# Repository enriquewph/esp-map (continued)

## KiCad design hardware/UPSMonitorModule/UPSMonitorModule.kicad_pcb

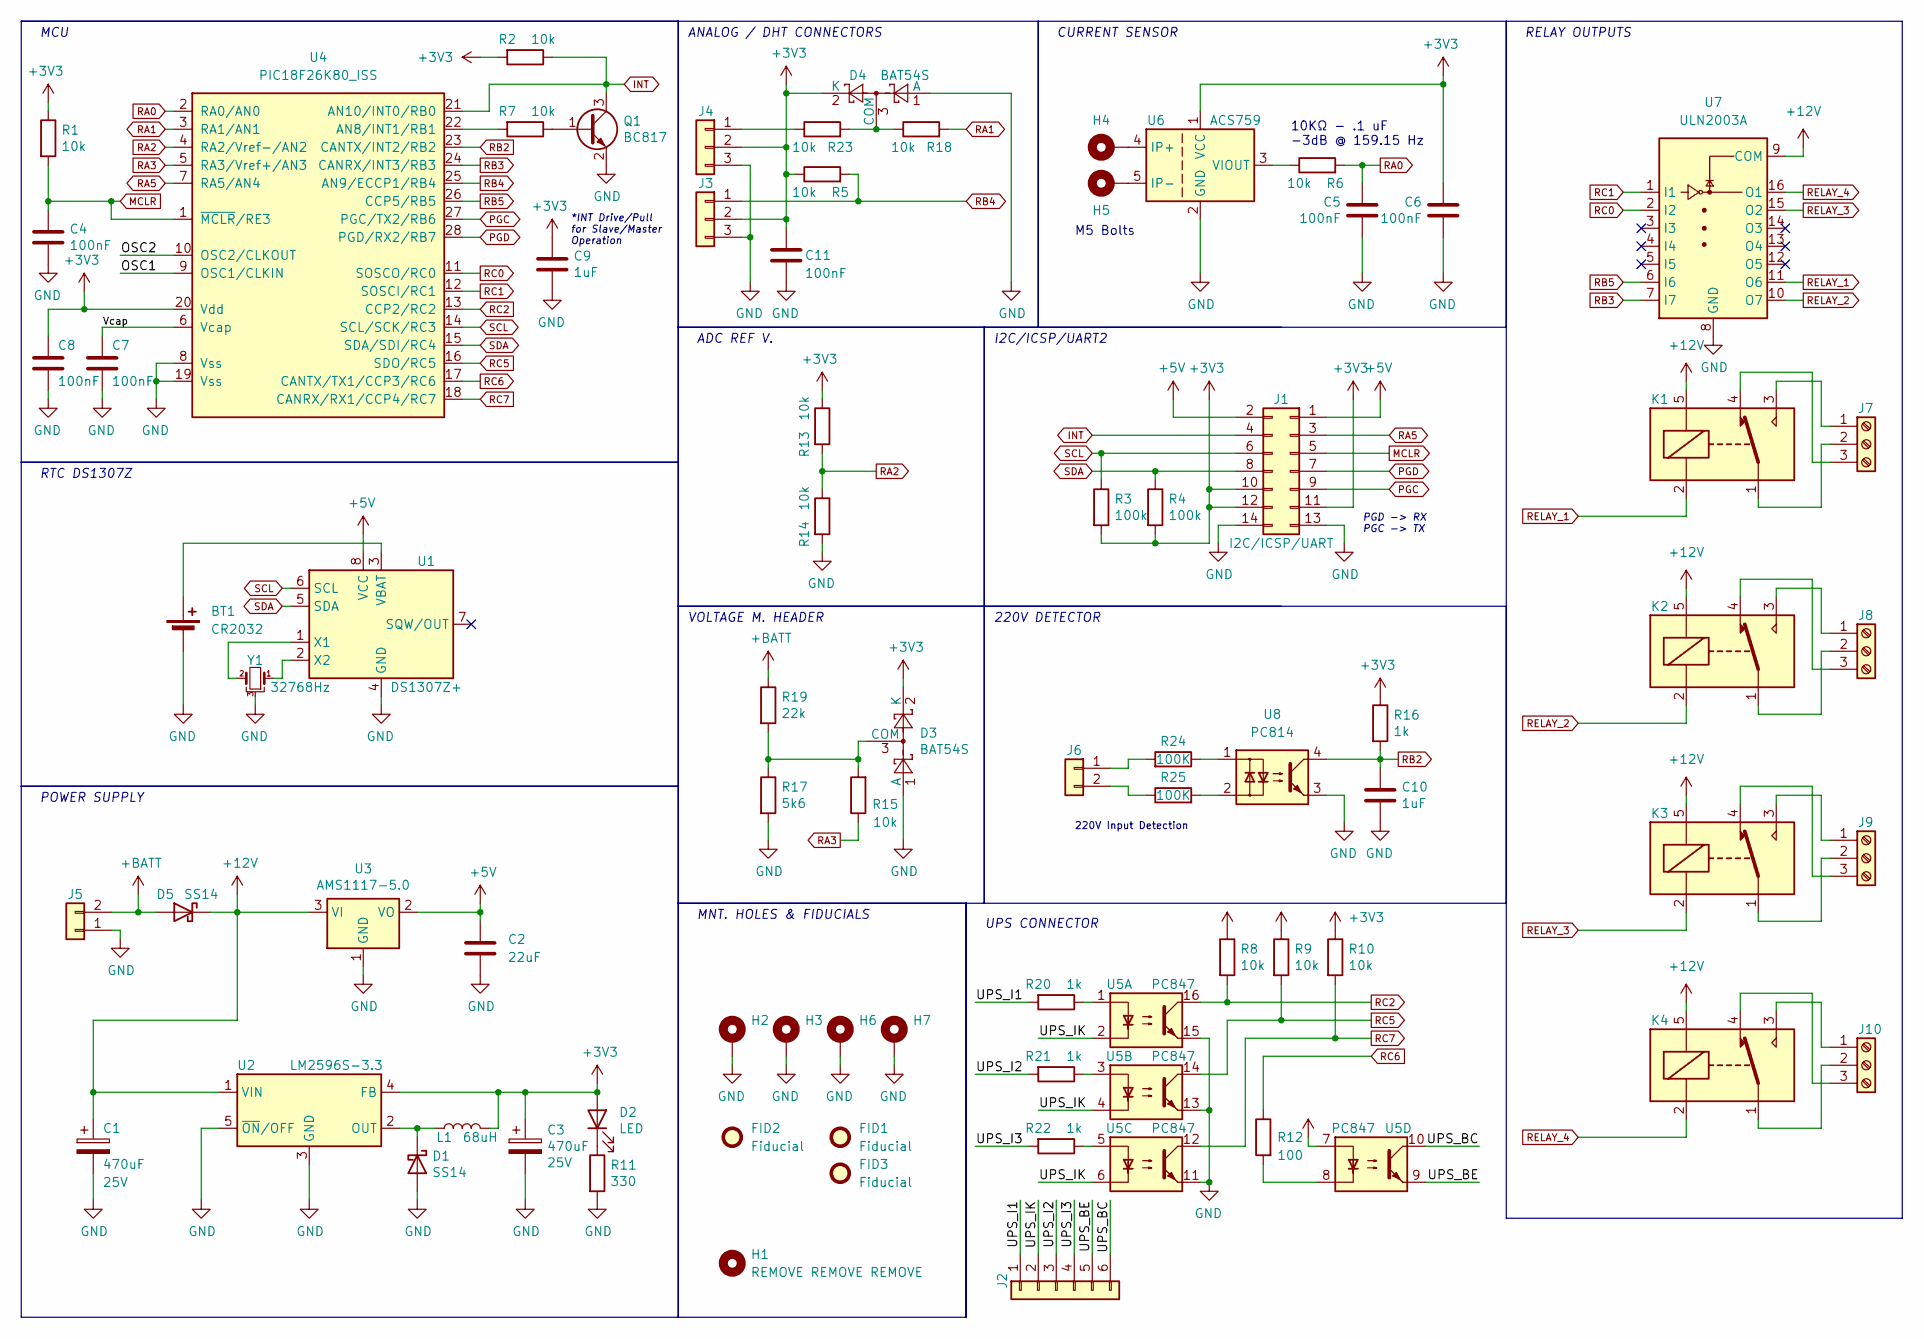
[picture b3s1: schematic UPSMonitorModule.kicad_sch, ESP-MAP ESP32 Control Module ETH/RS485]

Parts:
BT1: CR2032; BatteryHolder_CR2032
C1, C3: 470uF; CAP_10x10_SMD_THT; Voltage 25V
C2: 22uF; C_1812_4532Metric_Pad1.57x3.40mm_HandSolder
C4, C5, C6, C7, C8, C11: 100nF; C_1206_3216Metric_Pad1.33x1.80mm_HandSolder; Voltage 50V
C9, C10: 1uF; C_1206_3216Metric_Pad1.33x1.80mm_HandSolder; Voltage 50V
D1, D5: SS14; D_SMA_Handsoldering
D2: LED; LED_1206_3216Metric
D3, D4: BAT54S; SOT-23
FID1, FID2, FID3: Fiducial; Fiducial_0.5mm_Mask1mm
H1: REMOVE REMOVE REMOVE; ControlModule
H2, H3, H6, H7: MountingHole_Pad; MountingHole_3.5mm_Pad
H4, H5: MountingHole_Pad; MountingHole_5.3mm_M5_Pad_Via
J1: I2C/ICSP/UART; PinHeader_2x07_P2.54mm_Vertical_19mmh
J2: Conn_01x06; Molex_KK-254_AE-6410-06A_1x06_P2.54mm_Vertical
J3, J4: Conn_01x03; Molex_KK-254_AE-6410-03A_1x03_P2.54mm_Vertical
J5, J6: Conn_01x02; TerminalBlock-Bornier-2_P5.08mm
J7, J8, J9, J10: Screw_Terminal_01x03; TerminalBlock-Bornier-3_P5.08mm
K1, K2, K3, K4: RELAY; Relay_SPDT_SANYOU_SRD_Series_Form_C
L1: 68uH; L_12x12mm_H8mm
Q1: BC817; SOT-23
R1, R2, R5, R6, R7, R8, R9, R10, R13, R14, R15, R18, R23: 10k; R_1206_3216Metric
R3, R4: 100k; R_1206_3216Metric
R11: 330; R_1206_3216Metric
R12: 100; R_1206_3216Metric
R16, R20, R21, R22: 1k; R_1206_3216Metric
R17: 5k6; R_Axial_DIN0207_L6.3mm_D2.5mm_P2.54mm_Vertical
R19: 22k; R_Axial_DIN0207_L6.3mm_D2.5mm_P2.54mm_Vertical
R24, R25: 100K; R_Axial_DIN0309_L9.0mm_D3.2mm_P5.08mm_Vertical
U1: DS1307Z+; SOIC-8_3.9x4.9mm_P1.27mm
U2: LM2596S-3.3; TO-263-5_TabPin3
U3: AMS1117-5.0; SOT-223-3_TabPin2
U4: PIC18F26K80_ISS; SSOP-28_5.3x10.2mm_P0.65mm
U5: PC847; SMDIP-16_W9.53mm
U6: ACS759; Allegro_CB_PFF
U7: ULN2003A; SOIC-16_3.9x9.9mm_P1.27mm
U8: PC814; SMDIP-4_W9.53mm
Y1: 32768Hz; Crystal_C38-LF_D3.0mm_L8.0mm_Horizontal_1EP_style1

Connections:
+3V3: C3.1, C6.1, C8.1, C9.1, C11.1, D2.2 (A), D3.2 (K), D4.2 (K), J1.10, J1.11, J1.12, J3.2, J4.2, L1.2, R1.1, R2.2, R3.2, R4.2, R5.1, R8.1, R9.1, R10.1, R13.1, R16.1, U2.4 (FB), U4.20 (Vdd), U5.7, U6.1 (VCC)
+5V: C2.1, J1.1, J1.2, U1.8 (VCC), U3.2 (VO)
+12V: C1.1, D5.1 (K), K1.5, K2.5, K3.5, K4.5, U2.1 (VIN), U3.3 (VI), U7.9 (COM)
+BATT: D5.2 (A), J5.2, R19.1
/OSC1: U4.9 (OSC1/CLKIN)
/OSC2: U4.10 (OSC2/CLKOUT)
/UPS_BC: J2.6, U5.10
/UPS_BE: J2.5, U5.9
/UPS_I1: J2.1, R20.2
/UPS_I2: J2.3, R21.2
/UPS_I3: J2.4, R22.2
/UPS_IK: J2.2, U5.2, U5.4, U5.6
/Vcap: C7.1, U4.6 (Vcap)
GND: BT1.2 (-), C1.2, C2.2, C3.2, C4.2, C5.2, C6.2, C7.2, C8.2, C9.2, C10.2, C11.2, D1.2 (A), D3.1 (A), D4.1 (A), H2.1, H3.1, H6.1, H7.1, J1.13, J1.14, J3.3, J4.3, J5.1, Q1.2 (E), R11.2, R14.2, R17.2, U1.4 (GND), U2.3 (GND), U2.5 (~ON/OFF), U3.1 (GND), U4.8 (Vss), U4.19 (Vss), U5.11, U5.13, U5.15, U6.2 (GND), U7.8 (GND), U8.3, Y1.3
INT: J1.4, Q1.3 (C), R2.1, U4.21 (AN10/INT0/RB0)
MCLR: C4.1, J1.5, R1.2, U4.1 (~MCLR/RE3)
unnamed: BT1.1 (+), U1.3 (VBAT)
unnamed: D1.1 (K), L1.1, U2.2 (OUT)
unnamed: D2.1 (K), R11.1
unnamed: D4.3 (COM), R18.1, R23.2
unnamed: D3.3 (COM), R15.2, R17.1, R19.2
unnamed: J4.1, R23.1
unnamed: J6.1, R24.2
unnamed: J6.2, R25.1
unnamed: J7.1, K1.3
unnamed: J7.2, K1.1
unnamed: J7.3, K1.4
unnamed: J8.1, K2.3
unnamed: J8.2, K2.1
unnamed: J8.3, K2.4
unnamed: J9.1, K3.3
unnamed: J9.2, K3.1
unnamed: J9.3, K3.4
unnamed: J10.1, K4.3
unnamed: J10.2, K4.1
unnamed: J10.3, K4.4
unnamed: Q1.1 (B), R7.1
unnamed: R20.1, U5.1
unnamed: R21.1, U5.3
unnamed: R22.1, U5.5
unnamed: R24.1, U8.1
unnamed: R25.2, U8.2
unnamed: R12.2, U5.8
unnamed: R7.2, U4.22 (AN8/INT1/RB1)
unnamed: U1.1 (X1), Y1.2
unnamed: U1.2 (X2), Y1.1
unnamed: H4.1, U6.4 (IP+)
unnamed: H5.1, U6.5 (IP-)
unnamed: R6.1, U6.3 (VIOUT)
PGC: J1.9, U4.27 (PGC/TX2/RB6)
PGD: J1.7, U4.28 (PGD/RX2/RB7)
RA0: C5.1, R6.2, U4.2 (RA0/AN0)
RA1: R18.2, U4.3 (RA1/AN1)
RA2: R13.2, R14.1, U4.4 (RA2/Vref-/AN2)
RA3: R15.1, U4.5 (RA3/Vref+/AN3)
RA5: J1.3, U4.7 (RA5/AN4)
RB2: C10.1, R16.2, U4.23 (CANTX/INT2/RB2), U8.4
RB3: U4.24 (CANRX/INT3/RB3), U7.7 (I7)
RB4: J3.1, R5.2, U4.25 (AN9/ECCP1/RB4)
RB5: U4.26 (CCP5/RB5), U7.6 (I6)
RC0: U4.11 (SOSCO/RC0), U7.2 (I2)
RC1: U4.12 (SOSCI/RC1), U7.1 (I1)
RC2: R8.2, U4.13 (CCP2/RC2), U5.16
RC5: R9.2, U4.16 (SDO/RC5), U5.14
RC6: R12.1, U4.17 (CANTX/TX1/CCP3/RC6)
RC7: R10.2, U4.18 (CANRX/RX1/CCP4/RC7), U5.12
RELAY_1: K1.2, U7.11 (O6)
RELAY_2: K2.2, U7.10 (O7)
RELAY_3: K3.2, U7.15 (O2)
RELAY_4: K4.2, U7.16 (O1)
SCL: J1.6, R3.1, U1.6 (SCL), U4.14 (SCL/SCK/RC3)
SDA: J1.8, R4.1, U1.5 (SDA), U4.15 (SDA/SDI/RC4)

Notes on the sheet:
I2C/ICSP/UART2
VOLTAGE M. HEADER
UPS CONNECTOR
ANALOG / DHT CONNECTORS
220V DETECTOR
CURRENT SENSOR
PGD -> RX PGC -> TX
10KΩ - .1 uF -3dB @ 159.15 Hz
MNT. HOLES & FIDUCIALS
RTC DS1307Z
POWER SUPPLY
M5 Bolts
RELAY OUTPUTS
ADC REF V.
*INT Drive/Pull for Slave/Master Operation
220V Input Detection
MCU

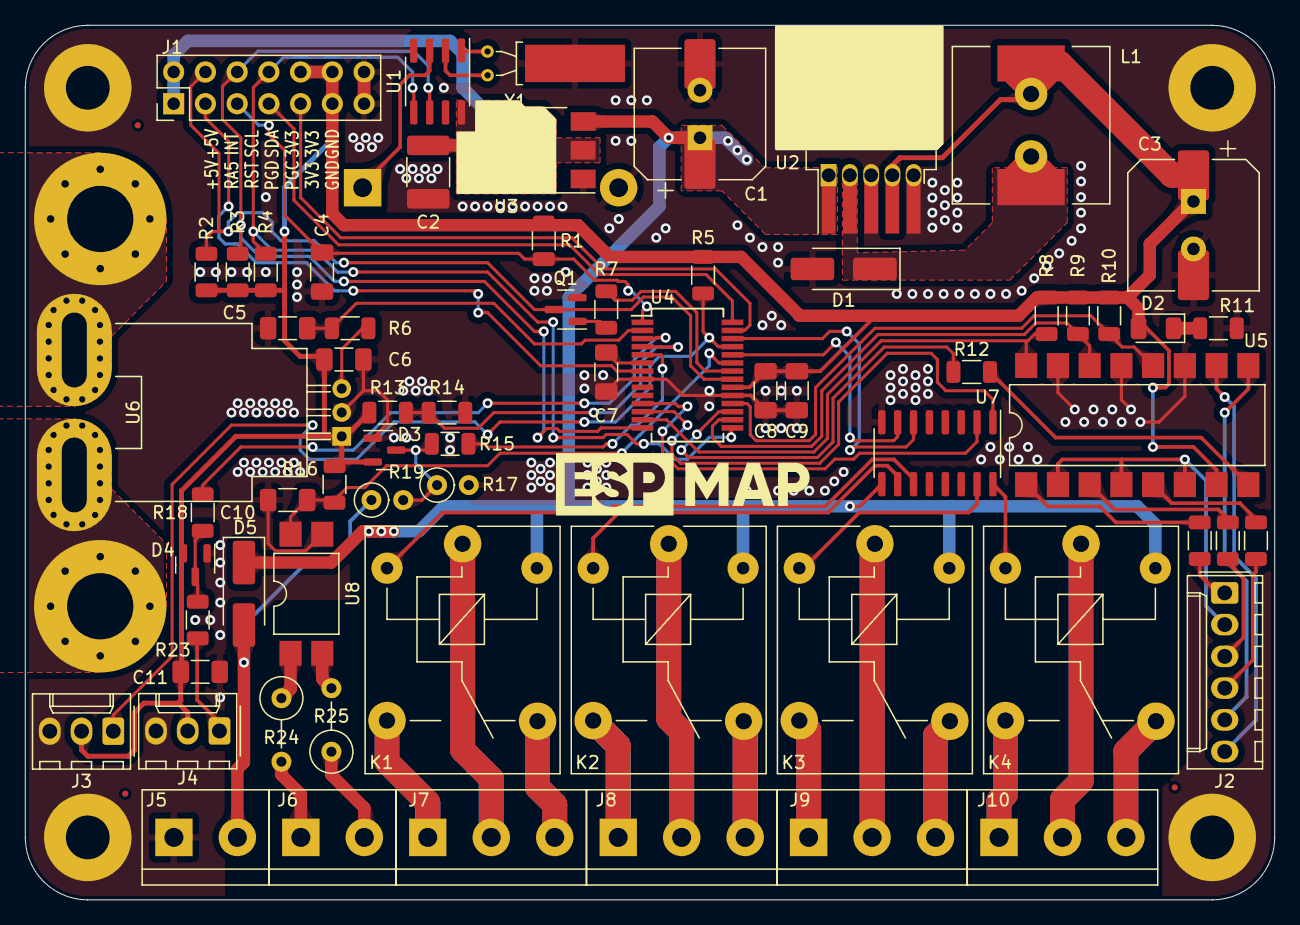
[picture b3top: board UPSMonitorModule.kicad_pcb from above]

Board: 2 copper layers, 100.0 x 70.0 mm, 76 parts (1 on the bottom side), 70 nets.

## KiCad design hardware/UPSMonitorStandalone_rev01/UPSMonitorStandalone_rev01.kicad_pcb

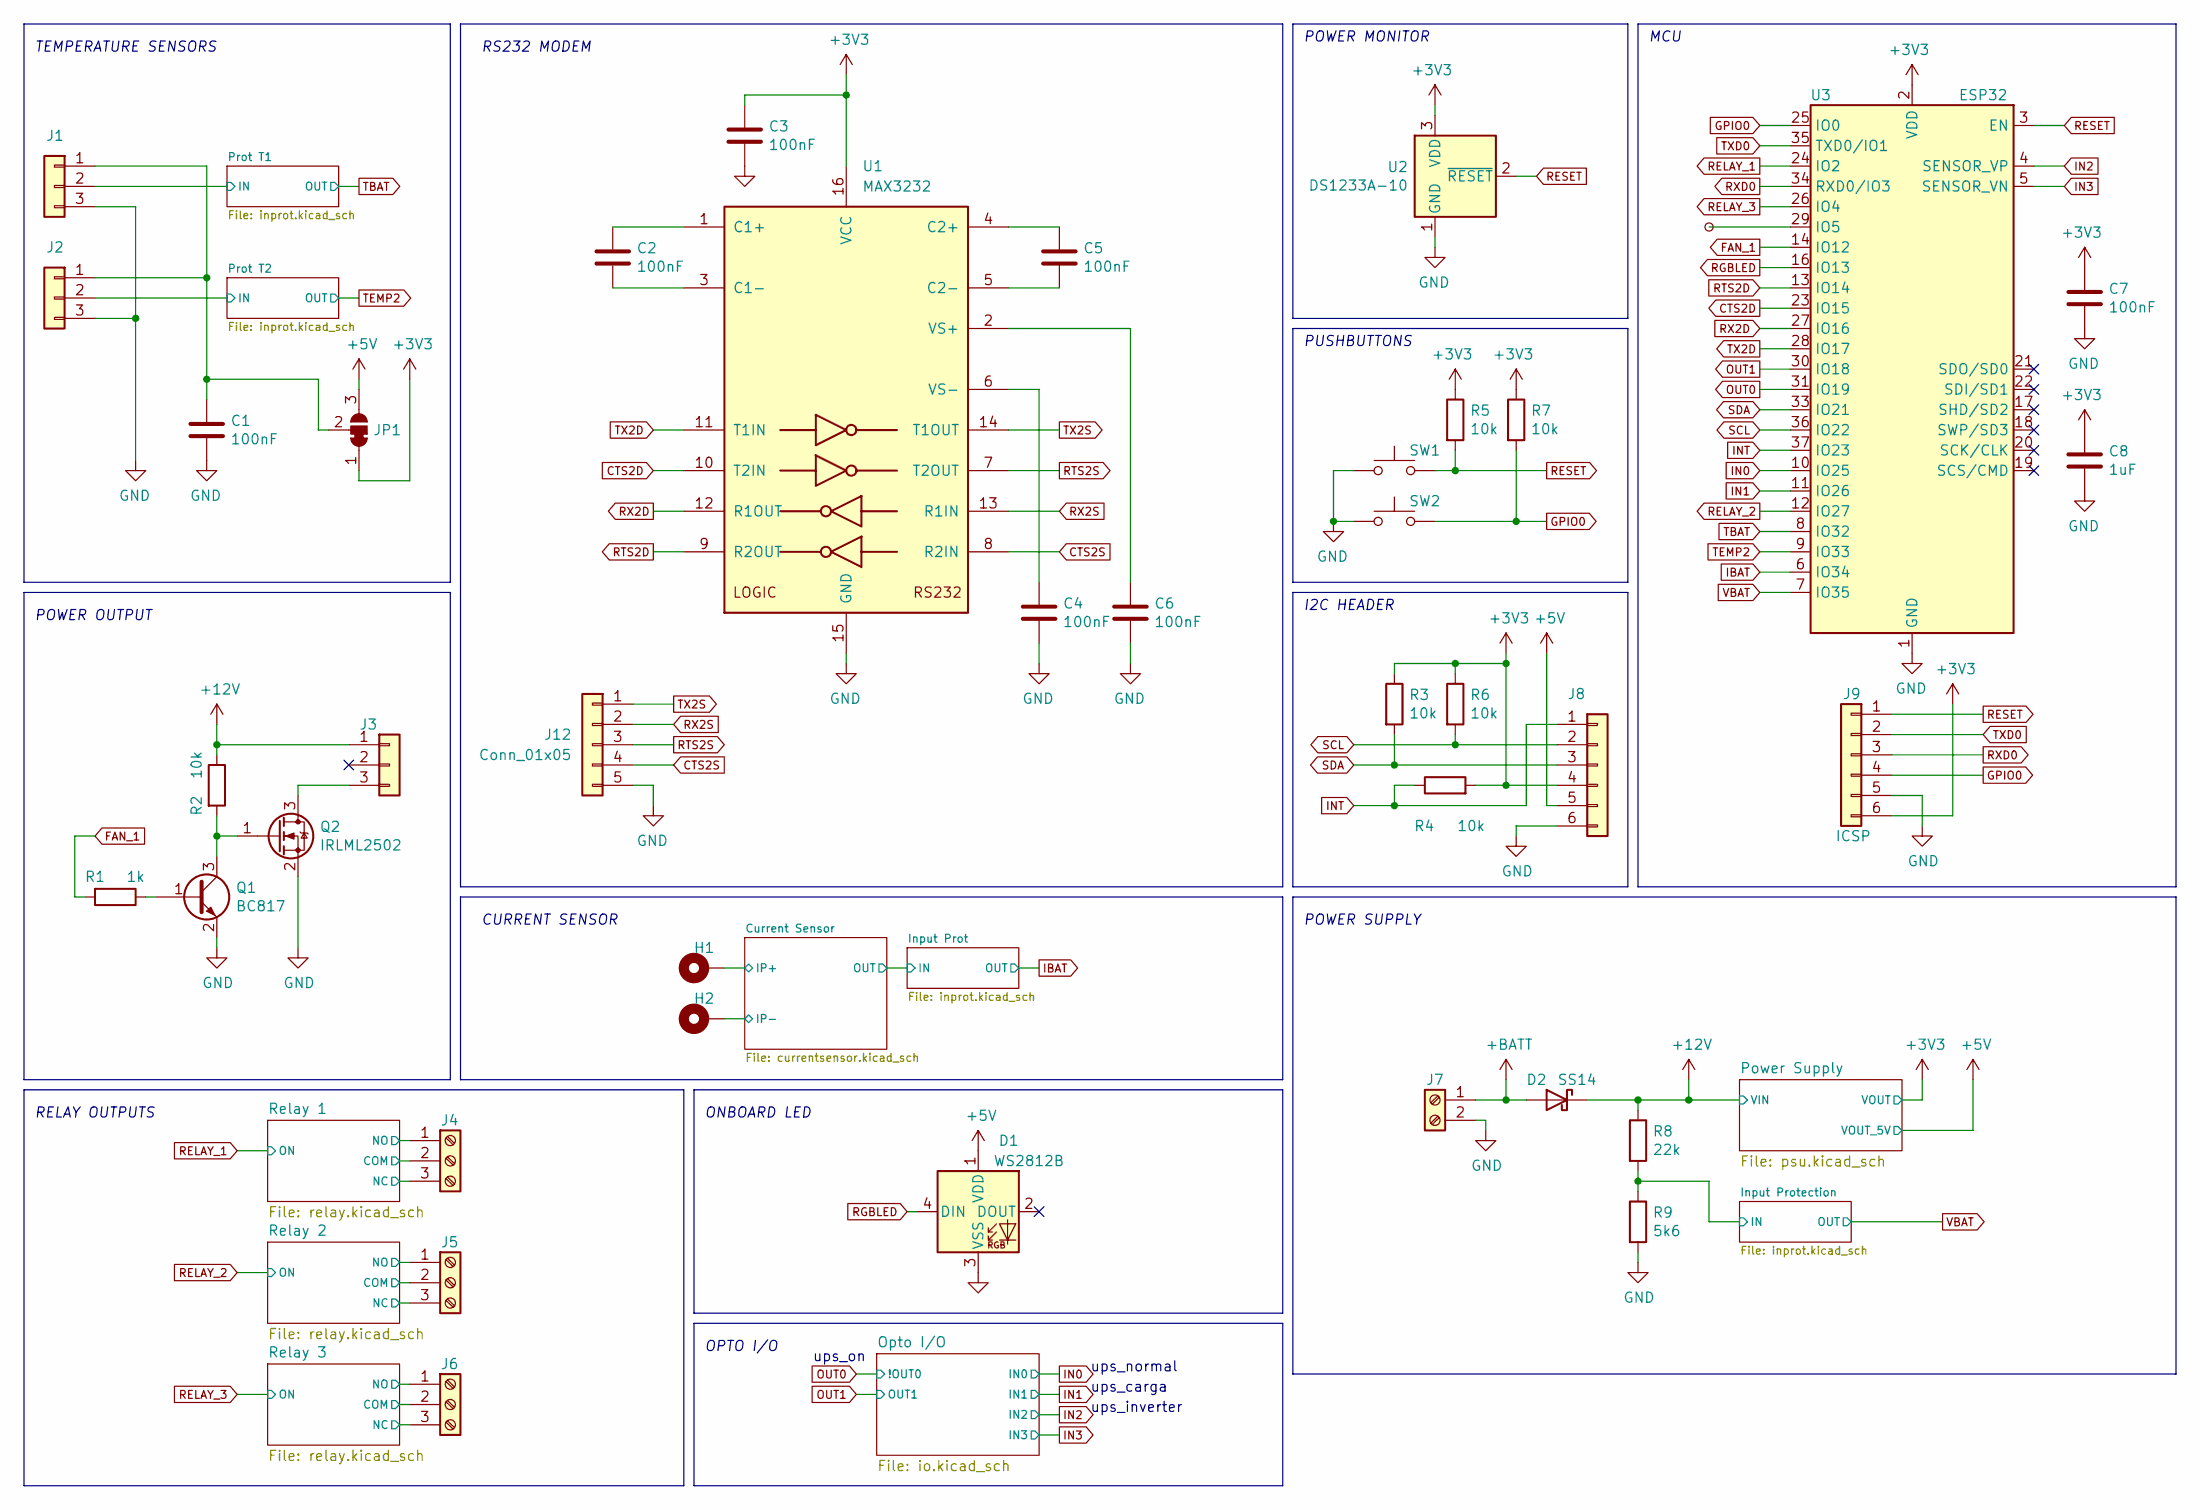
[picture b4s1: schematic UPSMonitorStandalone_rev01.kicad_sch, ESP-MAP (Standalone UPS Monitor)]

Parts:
C1, C7: 100nF; C_1206_3216Metric_Pad1.33x1.80mm_HandSolder; Voltage 50V
C2, C3, C4, C5, C6: 100nF; C_0603_1608Metric_Pad1.08x0.95mm_HandSolder; Voltage 50V
C8: 1uF; C_1206_3216Metric_Pad1.33x1.80mm_HandSolder; Voltage 50V
D1: WS2812B; LED_WS2812B_PLCC4_5.0x5.0mm_P3.2mm
D2: SS14; D_SMA_Handsoldering
H1, H2: MountingHole_Pad; MountingHole_4mm_Pad_Via
J1, J2, J3: Conn_01x03; Molex_KK-254_AE-6410-03A_1x03_P2.54mm_Vertical
J4, J5, J6: Screw_Terminal_01x03; TerminalBlock_bornier-3_P5.08mm
J7: Screw_Terminal_01x02; TerminalBlock_bornier-2_P5.08mm
J8: Conn_01x06; Molex_KK-254_AE-6410-06A_1x06_P2.54mm_Vertical
J9: ICSP; PinSocket_1x06_P2.54mm_Vertical
J12: Conn_01x05; PinSocket_1x05_P2.54mm_Vertical
JP1: SolderJumper_3_Bridged12; SolderJumper-3_P1.3mm_Open_RoundedPad1.0x1.5mm_NumberLabels
Q1: BC817; SOT-23
Q2: IRLML2502; SOT-23
R1: 1k; R_1206_3216Metric
R2, R3, R4, R5, R6, R7: 10k; R_1206_3216Metric
R8: 22k; R_1206_3216Metric
R9: 5k6; R_1206_3216Metric
SW1, SW2: SW_Push; SW_PUSH_6mm
TP1: TestPoint_Small; TestPoint_Pad_D1.0mm
U1: MAX3232; SOIC-16_3.9x9.9mm_P1.27mm
U2: DS1233A-10; TO-92
U3: ESP32; ESP32-WROOM-32

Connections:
+3V3: C3.1, C7.1, C8.1, J8.4, J9.6, JP1.1 (A), R3.1, R4.2, R5.1, R6.1, R7.1, U1.16 (VCC), U2.3 (VDD), U3.2 (VDD); also elsewhere on the board
+5V: D1.1 (VDD), J8.5, JP1.3 (B); also elsewhere on the board
+12V: D2.1 (K), J3.1, R2.1, R8.1; also elsewhere on the board
+BATT: D2.2 (A), J7.1
/Current Sensor/IP+: H1.1; also elsewhere on the board
/Current Sensor/IP-: H2.1; also elsewhere on the board
/Input Protection/IN: R8.2, R9.1; also elsewhere on the board
/Prot T1/IN: J1.2; also elsewhere on the board
/Prot T2/IN: J2.2; also elsewhere on the board
/Relay 1/COM: J4.2; also elsewhere on the board
/Relay 1/NC: J4.3; also elsewhere on the board
/Relay 1/NO: J4.1; also elsewhere on the board
/Relay 2/COM: J5.2; also elsewhere on the board
/Relay 2/NC: J5.3; also elsewhere on the board
/Relay 2/NO: J5.1; also elsewhere on the board
/Relay 3/COM: J6.2; also elsewhere on the board
/Relay 3/NC: J6.3; also elsewhere on the board
/Relay 3/NO: J6.1; also elsewhere on the board
CTS2D: U1.10 (T2IN), U3.23 (IO15)
CTS2S: J12.4, U1.8 (R2IN)
FAN_1: R1.2, U3.14 (IO12)
GND: C1.2, C3.2, C4.2, C6.2, C7.2, C8.2, D1.3 (VSS), J1.3, J2.3, J7.2, J8.6, J9.5, J12.5, Q1.2 (E), Q2.2 (S), R9.2, SW1.1, SW2.1, U1.15 (GND), U2.1 (GND), U3.1 (GND), U3.15 (GND), U3.38 (GND), U3.39 (GND); also elsewhere on the board
GPIO0: J9.4, R7.2, SW2.2, U3.25 (IO0)
IBAT: U3.6 (IO34); also elsewhere on the board
IN0: U3.10 (IO25); also elsewhere on the board
IN1: U3.11 (IO26); also elsewhere on the board
IN2: U3.4 (SENSOR_VP); also elsewhere on the board
IN3: U3.5 (SENSOR_VN); also elsewhere on the board
INT: J8.1, R4.1, U3.37 (IO23)
unnamed: C1.1, J1.1, J2.1, JP1.2 (C)
unnamed: J3.3, Q2.3 (D)
unnamed: Q1.1 (B), R1.1
unnamed: Q1.3 (C), Q2.1 (G), R2.2
unnamed: C2.1, U1.1 (C1+)
unnamed: C2.2, U1.3 (C1-)
unnamed: C5.1, U1.4 (C2+)
unnamed: C5.2, U1.5 (C2-)
unnamed: C6.1, U1.2 (VS+)
unnamed: C4.1, U1.6 (VS-)
unnamed: TP1.1, U3.29 (IO5)
OUT0: U3.31 (IO19); also elsewhere on the board
OUT1: U3.30 (IO18); also elsewhere on the board
RELAY_1: U3.24 (IO2); also elsewhere on the board
RELAY_2: U3.12 (IO27); also elsewhere on the board
RELAY_3: U3.26 (IO4); also elsewhere on the board
RESET: J9.1, R5.2, SW1.2, U2.2 (~RESET), U3.3 (EN)
RGBLED: D1.4 (DIN), U3.16 (IO13)
RTS2D: U1.9 (R2OUT), U3.13 (IO14)
RTS2S: J12.3, U1.7 (T2OUT)
RX2D: U1.12 (R1OUT), U3.27 (IO16)
RX2S: J12.2, U1.13 (R1IN)
RXD0: J9.3, U3.34 (RXD0/IO3)
SCL: J8.2, R6.2, U3.36 (IO22)
SDA: J8.3, R3.2, U3.33 (IO21)
TBAT: U3.8 (IO32); also elsewhere on the board
TEMP2: U3.9 (IO33); also elsewhere on the board
TX2D: U1.11 (T1IN), U3.28 (IO17)
TX2S: J12.1, U1.14 (T1OUT)
TXD0: J9.2, U3.35 (TXD0/IO1)
VBAT: U3.7 (IO35); also elsewhere on the board

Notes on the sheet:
POWER SUPPLY
I2C HEADER
ONBOARD LED
ups_normal
PUSHBUTTONS
POWER OUTPUT
ups_carga
ups_on
POWER MONITOR
RELAY OUTPUTS
MCU
RS232 MODEM
OPTO I/O
ups_inverter
CURRENT SENSOR
TEMPERATURE SENSORS

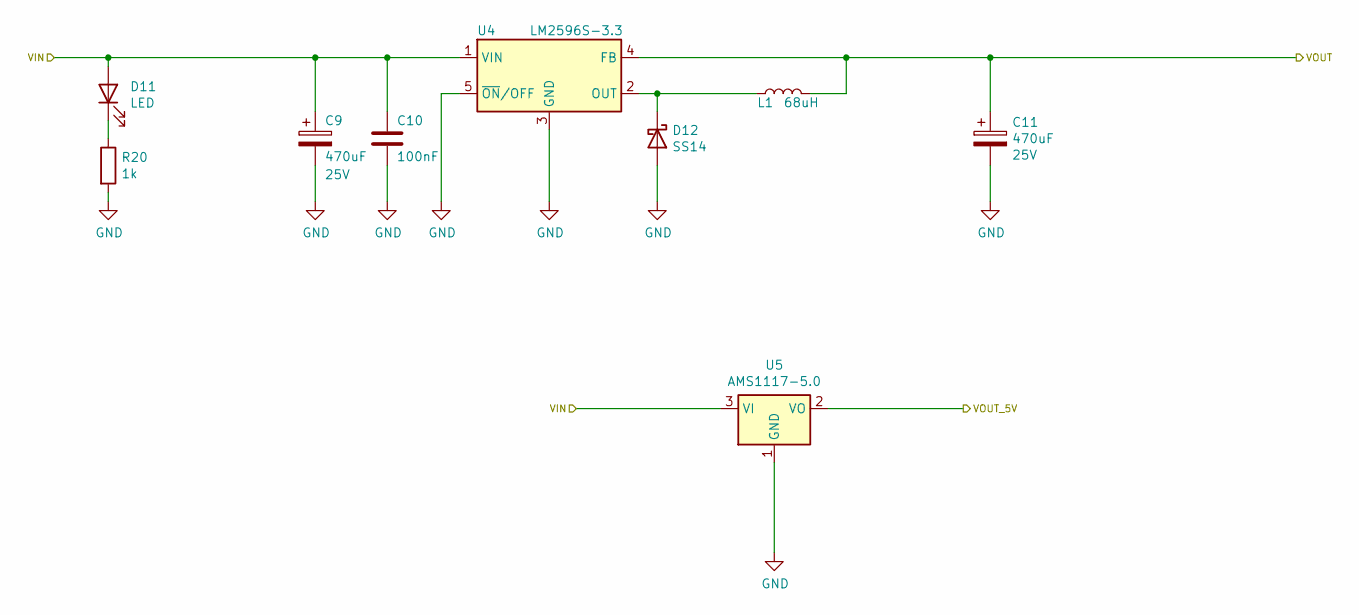
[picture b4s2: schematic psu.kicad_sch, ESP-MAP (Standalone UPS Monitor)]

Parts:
C9, C11: 470uF; CAP_10x10_SMD_THT; Voltage 25V
C10: 100nF; C_1206_3216Metric_Pad1.33x1.80mm_HandSolder; Voltage 50V
D11: LED; LED_1206_3216Metric
D12: SS14; D_SMA_Handsoldering
L1: 68uH; L_12x12mm_H8mm
R20: 1k; R_1206_3216Metric
U4: LM2596S-3.3; TO-263-5_TabPin3
U5: AMS1117-5.0; SOT-223-3_TabPin2

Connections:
+3V3: C11.1, L1.2, U4.4 (FB); also elsewhere on the board
+5V: U5.2 (VO); also elsewhere on the board
+12V: C9.1, C10.1, D11.2 (A), U4.1 (VIN), U5.3 (VI); also elsewhere on the board
GND: C9.2, C10.2, C11.2, D12.2 (A), R20.2, U4.3 (GND), U4.5 (~ON/OFF), U5.1 (GND); also elsewhere on the board
unnamed: D11.1 (K), R20.1
unnamed: D12.1 (K), L1.1, U4.2 (OUT)

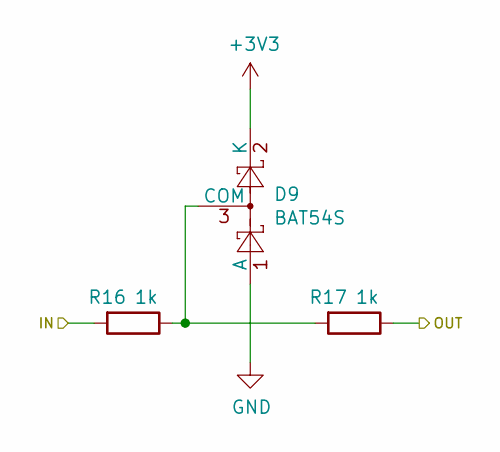
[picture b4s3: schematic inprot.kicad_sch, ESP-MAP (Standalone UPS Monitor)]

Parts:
D9: BAT54S; SOT-23
R16, R17: 1k; R_1206_3216Metric

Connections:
+3V3: D9.2 (K); also elsewhere on the board
/Prot T1/IN: R16.2; also elsewhere on the board
GND: D9.1 (A); also elsewhere on the board
unnamed: D9.3 (COM), R16.1, R17.2
TBAT: R17.1; also elsewhere on the board

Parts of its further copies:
D10, D13, D14: BAT54S; SOT-23
R18, R19, R21, R22, R25, R26: 1k; R_1206_3216Metric

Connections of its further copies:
+3V3: D10.2 (K), D13.2 (K), D14.2 (K); also elsewhere on the board
/Current Sensor/OUT: R25.2; also elsewhere on the board
/Input Protection/IN: R21.2; also elsewhere on the board
/Prot T2/IN: R18.2; also elsewhere on the board
GND: D10.1 (A), D13.1 (A), D14.1 (A); also elsewhere on the board
IBAT: R26.1; also elsewhere on the board
unnamed: D10.3 (COM), R18.1, R19.2
unnamed: D13.3 (COM), R21.1, R22.2
unnamed: D14.3 (COM), R25.1, R26.2
TEMP2: R19.1; also elsewhere on the board
VBAT: R22.1; also elsewhere on the board

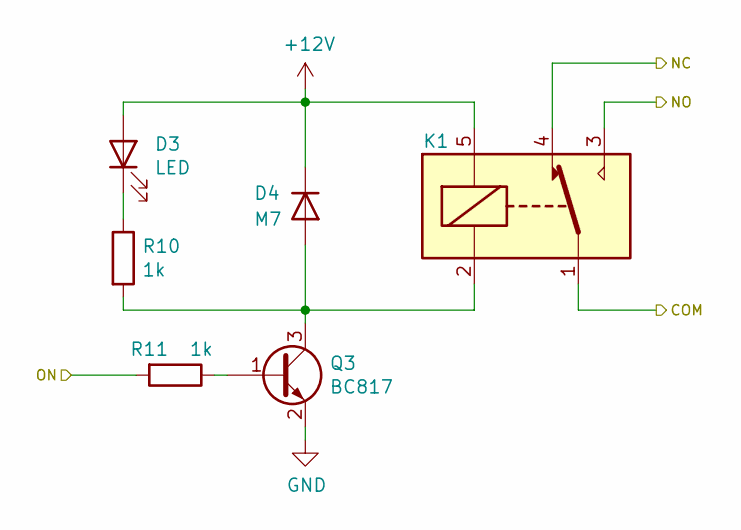
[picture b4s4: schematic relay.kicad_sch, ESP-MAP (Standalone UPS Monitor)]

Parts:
D3: LED; LED_1206_3216Metric
D4: M7; D_SMA_Handsoldering
K1: RELAY; Relay_SPDT_SANYOU_SRD_Series_Form_C
Q3: BC817; SOT-23
R10, R11: 1k; R_1206_3216Metric

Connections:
+12V: D3.2 (A), D4.1 (K), K1.5; also elsewhere on the board
/Relay 1/COM: K1.1; also elsewhere on the board
/Relay 1/NC: K1.4; also elsewhere on the board
/Relay 1/NO: K1.3; also elsewhere on the board
GND: Q3.2 (E); also elsewhere on the board
unnamed: D3.1 (K), R10.1
unnamed: D4.2 (A), K1.2, Q3.3 (C), R10.2
unnamed: Q3.1 (B), R11.1
RELAY_1: R11.2; also elsewhere on the board

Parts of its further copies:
D5, D7: LED; LED_1206_3216Metric
D6, D8: M7; D_SMA_Handsoldering
K2, K3: RELAY; Relay_SPDT_SANYOU_SRD_Series_Form_C
Q4, Q5: BC817; SOT-23
R12, R13, R14, R15: 1k; R_1206_3216Metric

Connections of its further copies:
+12V: D5.2 (A), D6.1 (K), D7.2 (A), D8.1 (K), K2.5, K3.5; also elsewhere on the board
/Relay 2/COM: K2.1; also elsewhere on the board
/Relay 2/NC: K2.4; also elsewhere on the board
/Relay 2/NO: K2.3; also elsewhere on the board
/Relay 3/COM: K3.1; also elsewhere on the board
/Relay 3/NC: K3.4; also elsewhere on the board
/Relay 3/NO: K3.3; also elsewhere on the board
GND: Q4.2 (E), Q5.2 (E); also elsewhere on the board
unnamed: D5.1 (K), R12.1
unnamed: D6.2 (A), K2.2, Q4.3 (C), R12.2
unnamed: D7.1 (K), R14.1
unnamed: D8.2 (A), K3.2, Q5.3 (C), R14.2
unnamed: Q4.1 (B), R13.1
unnamed: Q5.1 (B), R15.1
RELAY_2: R13.2; also elsewhere on the board
RELAY_3: R15.2; also elsewhere on the board

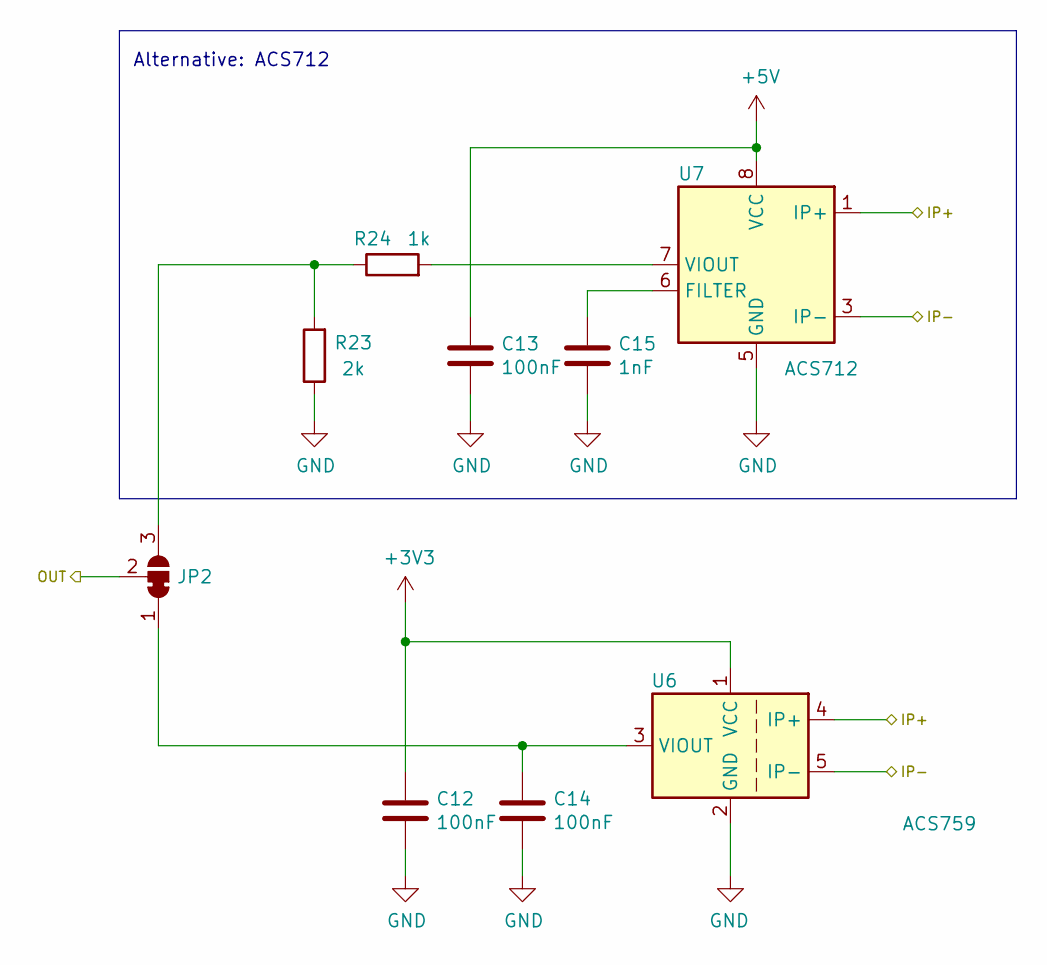
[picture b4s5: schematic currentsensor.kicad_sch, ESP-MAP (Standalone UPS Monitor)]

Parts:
C12, C13, C14: 100nF; C_1206_3216Metric_Pad1.33x1.80mm_HandSolder; Voltage 50V
C15: 1nF; C_1206_3216Metric_Pad1.33x1.80mm_HandSolder
JP2: SolderJumper_3_Bridged12; SolderJumper-3_P1.3mm_Open_RoundedPad1.0x1.5mm_NumberLabels
R23: 2k; R_1206_3216Metric
R24: 1k; R_1206_3216Metric
U6: ACS759; Allegro_CB_PFF
U7: ACS712; SOIC-8_3.9x4.9mm_P1.27mm

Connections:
+3V3: C12.1, U6.1 (VCC); also elsewhere on the board
+5V: C13.1, U7.8 (VCC); also elsewhere on the board
/Current Sensor/IP+: U6.4 (IP+), U7.1 (IP+), U7.2 (IP+); also elsewhere on the board
/Current Sensor/IP-: U6.5 (IP-), U7.3 (IP-), U7.4 (IP-); also elsewhere on the board
/Current Sensor/OUT: JP2.2 (C); also elsewhere on the board
GND: C12.2, C13.2, C14.2, C15.2, R23.1, U6.2 (GND), U7.5 (GND); also elsewhere on the board
unnamed: C14.1, JP2.1 (A), U6.3 (VIOUT)
unnamed: JP2.3 (B), R23.2, R24.1
unnamed: C15.1, U7.6 (FILTER)
unnamed: R24.2, U7.7 (VIOUT)

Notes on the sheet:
Alternative: ACS712

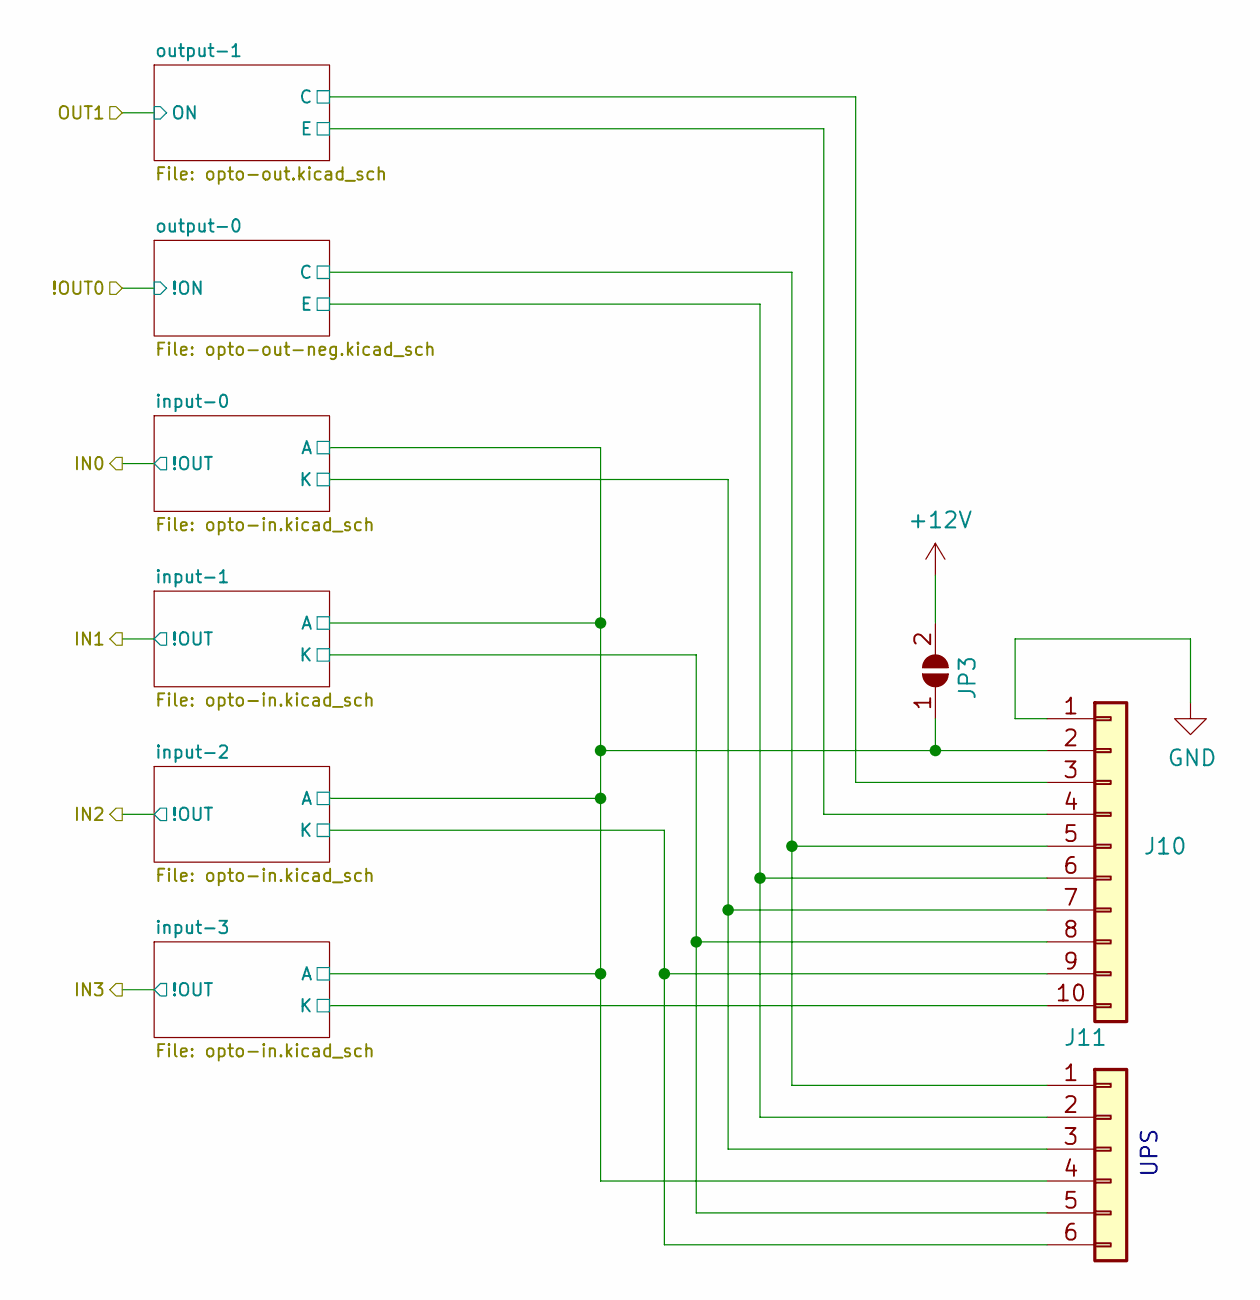
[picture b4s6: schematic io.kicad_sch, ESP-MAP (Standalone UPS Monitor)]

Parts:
J10: Conn_01x10; Molex_KK-254_AE-6410-10A_1x10_P2.54mm_Vertical
J11: Conn_01x06; Molex_KK-254_AE-6410-06A_1x06_P2.54mm_Vertical
JP3: SolderJumper_2_Open; SolderJumper-2_P1.3mm_Open_RoundedPad1.0x1.5mm

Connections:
+12V: JP3.2 (B); also elsewhere on the board
/Opto I/O/input-0/A: J10.2, J11.4, JP3.1 (A); also elsewhere on the board
/Opto I/O/input-0/K: J10.7, J11.3; also elsewhere on the board
/Opto I/O/input-1/K: J10.8, J11.5; also elsewhere on the board
/Opto I/O/input-2/K: J10.9, J11.6; also elsewhere on the board
/Opto I/O/input-3/K: J10.10; also elsewhere on the board
/Opto I/O/output-0/C: J10.5, J11.1; also elsewhere on the board
/Opto I/O/output-0/E: J10.6, J11.2; also elsewhere on the board
/Opto I/O/output-1/C: J10.3; also elsewhere on the board
/Opto I/O/output-1/E: J10.4; also elsewhere on the board
GND: J10.1; also elsewhere on the board

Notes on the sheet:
UPS

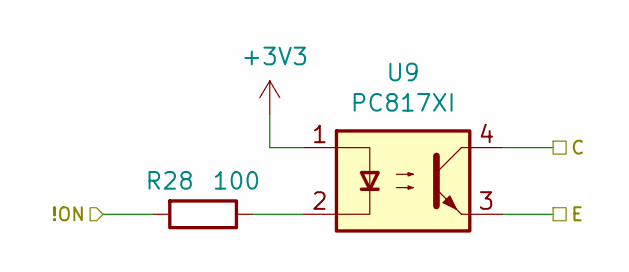
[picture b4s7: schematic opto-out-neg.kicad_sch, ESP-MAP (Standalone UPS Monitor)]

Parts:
R28: 100; R_1206_3216Metric
U9: PC817XI; SMDIP-4_W9.53mm

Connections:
+3V3: U9.1; also elsewhere on the board
/Opto I/O/output-0/C: U9.4; also elsewhere on the board
/Opto I/O/output-0/E: U9.3; also elsewhere on the board
unnamed: R28.1, U9.2
OUT0: R28.2; also elsewhere on the board

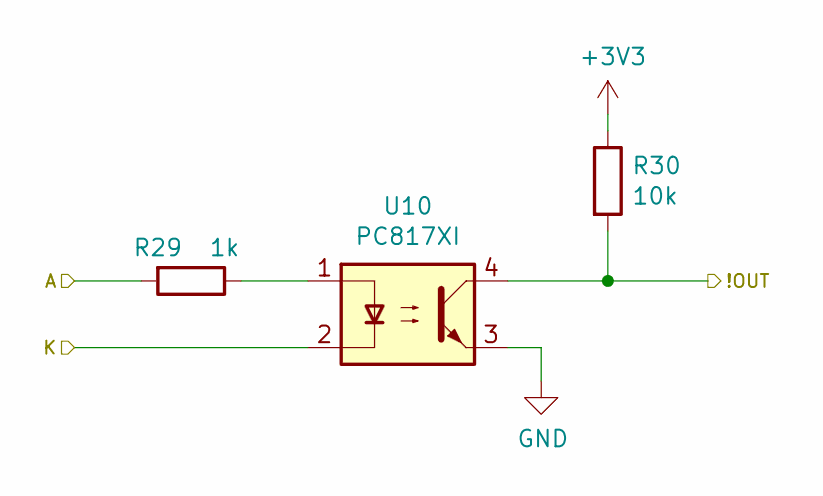
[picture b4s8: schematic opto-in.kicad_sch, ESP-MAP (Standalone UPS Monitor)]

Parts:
R29: 1k; R_1206_3216Metric
R30: 10k; R_1206_3216Metric
U10: PC817XI; SMDIP-4_W9.53mm

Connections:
+3V3: R30.1; also elsewhere on the board
/Opto I/O/input-0/A: R29.2; also elsewhere on the board
/Opto I/O/input-0/K: U10.2; also elsewhere on the board
GND: U10.3; also elsewhere on the board
IN0: R30.2, U10.4; also elsewhere on the board
unnamed: R29.1, U10.1

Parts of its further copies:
R31, R33, R35: 1k; R_1206_3216Metric
R32, R34, R36: 10k; R_1206_3216Metric
U11, U12, U13: PC817XI; SMDIP-4_W9.53mm

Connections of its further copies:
+3V3: R32.1, R34.1, R36.1; also elsewhere on the board
/Opto I/O/input-0/A: R31.2, R33.2, R35.2; also elsewhere on the board
/Opto I/O/input-1/K: U11.2; also elsewhere on the board
/Opto I/O/input-2/K: U12.2; also elsewhere on the board
/Opto I/O/input-3/K: U13.2; also elsewhere on the board
GND: U11.3, U12.3, U13.3; also elsewhere on the board
IN1: R32.2, U11.4; also elsewhere on the board
IN2: R34.2, U12.4; also elsewhere on the board
IN3: R36.2, U13.4; also elsewhere on the board
unnamed: R31.1, U11.1
unnamed: R33.1, U12.1
unnamed: R35.1, U13.1

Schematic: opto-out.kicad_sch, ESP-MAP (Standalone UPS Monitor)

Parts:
R27: 100; R_1206_3216Metric
U8: PC817XI; SMDIP-4_W9.53mm

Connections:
/Opto I/O/output-1/C: U8.4; also elsewhere on the board
/Opto I/O/output-1/E: U8.3; also elsewhere on the board
GND: U8.2; also elsewhere on the board
unnamed: R27.1, U8.1
OUT1: R27.2; also elsewhere on the board
